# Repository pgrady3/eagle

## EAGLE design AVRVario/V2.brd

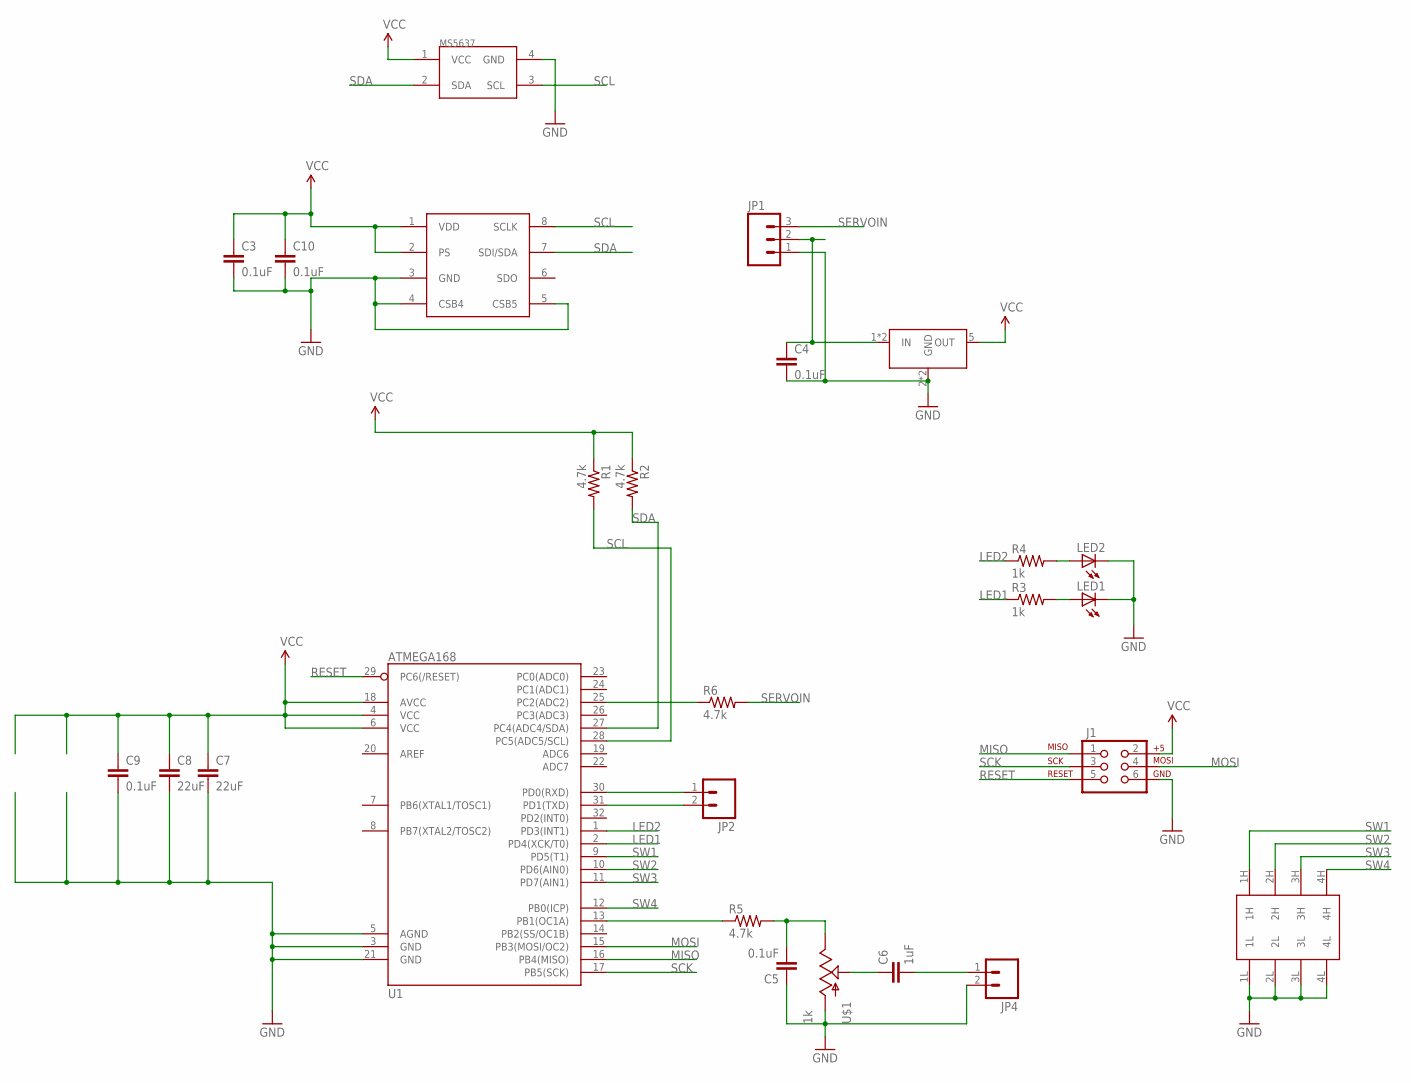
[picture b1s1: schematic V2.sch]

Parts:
C3, C4, C5, C9, C10: 0.1uF; 0603-CAP
C6: 1uF; 0603-CAP
C7, C8: 22uF; 0805
J1: AVR_SPI_PRG_6NS; 2X3-NS
JP1: M03PTH; 1X03
JP2, JP4: M02PTH; 1X02
LED1, LED2: LED0603; LED-0603
R1, R2, R5, R6: 4.7k; 0603-RES
R3, R4: 1k; 0603-RES
U1: ATMEGA168; TQFP32-08
U$1: 1k; BOURNS_3306KPW
U$2: MS5611
U$3: LINEAR_REGSOT23-5_TOREX; SOT23-5
U$4: MS5637
U$5: DIP_SWITCH; DIPSWITCH4

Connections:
GND: C3.2, C4.2, C5.1, C7.2, C8.2, C9.2, C10.2, J1.6, JP1.1, JP4.2, LED1.C, LED2.C, U1.3 (GND), U1.5 (AGND), U1.21 (GND), U$1.3 (A), U$2.3 (GND), U$2.4 (CSB4), U$2.5 (CSB5), U$3.2 (GND), U$3.3 (GND), U$4.4 (GND), U$5.1L, U$5.2L, U$5.3L, U$5.4L
LED1: R3.1, U1.2 (PD4(XCK/T0))
LED2: R4.1, U1.1 (PD3(INT1))
MISO: J1.1, U1.16 (PB4(MISO))
MOSI: J1.4, U1.15 (PB3(MOSI/OC2))
unnamed: R6.1, U1.25 (PC2(ADC2))
unnamed: C4.1, JP1.2, U$3.1 (IN), U$3.4 (IN)
unnamed: JP2.1, U1.30 (PD0(RXD))
unnamed: LED2.A, R4.2
unnamed: LED1.A, R3.2
unnamed: JP2.2, U1.31 (PD1(TXD))
unnamed: R5.1, U1.13 (PB1(OC1A))
unnamed: C5.2, R5.2, U$1.1 (E)
unnamed: C6.1, U$1.2 (S)
unnamed: C6.2, JP4.1
RESET: J1.5, U1.29 (PC6(/RESET))
SCK: J1.3, U1.17 (PB5(SCK))
SCL: R1.2, U1.28 (PC5(ADC5/SCL)), U$2.8 (SCLK), U$4.3 (SCL)
SDA: R2.2, U1.27 (PC4(ADC4/SDA)), U$2.7 (SDI/SDA), U$4.2 (SDA)
SERVOIN: JP1.3, R6.2
SW1: U1.9 (PD5(T1)), U$5.1H
SW2: U1.10 (PD6(AIN0)), U$5.2H
SW3: U1.11 (PD7(AIN1)), U$5.3H
SW4: U1.12 (PB0(ICP)), U$5.4H
VCC: C3.1, C7.1, C8.1, C9.1, C10.1, J1.2, R1.1, R2.1, U1.4 (VCC), U1.6 (VCC), U1.18 (AVCC), U$2.1 (VDD), U$2.2 (PS), U$3.5 (OUT), U$4.1 (VCC)

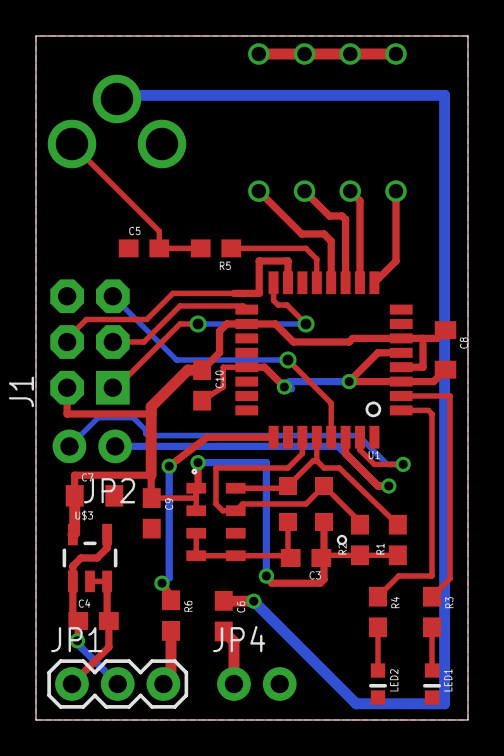
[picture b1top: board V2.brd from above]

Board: 2 copper layers, 24.0 x 38.0 mm, 26 parts (0 on the bottom side), 25 nets.

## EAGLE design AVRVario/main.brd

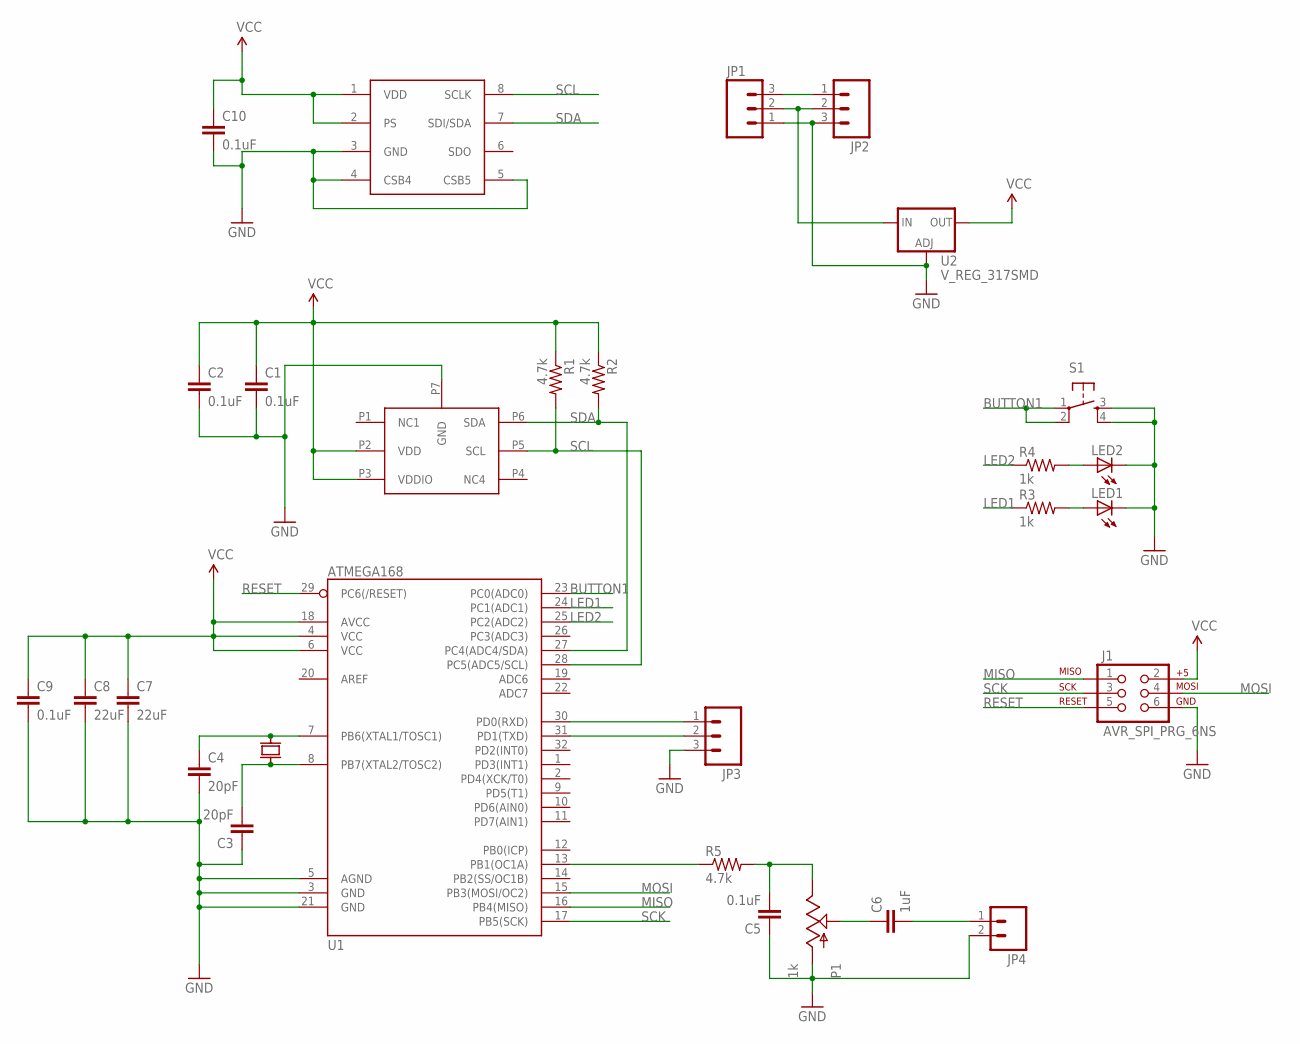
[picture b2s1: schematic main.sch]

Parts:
C1, C2, C5, C9, C10: 0.1uF; 0603-CAP
C3, C4: 20pF; 0603-CAP
C6: 1uF; 0603-CAP
C7, C8: 22uF; 0805
J1: AVR_SPI_PRG_6NS; 2X3-NS
JP1, JP2, JP3: M03PTH; 1X03
JP4: M02PTH; 1X02
LED1, LED2: LED0603; LED-0603
P1: 1k; TRIM_POT
R1, R2, R5: 4.7k; 0603-RES
R3, R4: 1k; 0603-RES
S1: TAC_SWITCHSMD; TACTILE_SWITCH_SMD
U1: ATMEGA168; TQFP32-08
U2: V_REG_317SMD; SOT223
U$1: BMP180
U$2: MS5611
U$3: 16M; HC49/US_7X4

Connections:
BUTTON1: S1.1, S1.2, U1.23 (PC0(ADC0))
GND: C1.2, C2.2, C3.1, C4.2, C5.1, C7.2, C8.2, C9.2, C10.2, J1.6, JP1.1, JP2.3, JP3.3, JP4.2, LED1.C, LED2.C, P1.3 (A), S1.3, S1.4, U1.3 (GND), U1.5 (AGND), U1.21 (GND), U2.1 (ADJ), U$1.P7 (GND), U$2.3 (GND), U$2.4 (CSB4), U$2.5 (CSB5)
LED1: R3.1, U1.24 (PC1(ADC1))
LED2: R4.1, U1.25 (PC2(ADC2))
MISO: J1.1, U1.16 (PB4(MISO))
MOSI: J1.4, U1.15 (PB3(MOSI/OC2))
unnamed: JP1.3, JP2.1
unnamed: C4.1, U1.7 (PB6(XTAL1/TOSC1)), U$3.P2
unnamed: C3.2, U1.8 (PB7(XTAL2/TOSC2)), U$3.P1
unnamed: JP1.2, JP2.2, U2.3 (IN)
unnamed: JP3.1, U1.30 (PD0(RXD))
unnamed: LED2.A, R4.2
unnamed: LED1.A, R3.2
unnamed: JP3.2, U1.31 (PD1(TXD))
unnamed: R5.1, U1.13 (PB1(OC1A))
unnamed: C5.2, P1.2 (E), R5.2
unnamed: C6.1, P1.1 (S)
unnamed: C6.2, JP4.1
RESET: J1.5, U1.29 (PC6(/RESET))
SCK: J1.3, U1.17 (PB5(SCK))
SCL: R1.2, U1.28 (PC5(ADC5/SCL)), U$1.P5 (SCL), U$2.8 (SCLK)
SDA: R2.2, U1.27 (PC4(ADC4/SDA)), U$1.P6 (SDA), U$2.7 (SDI/SDA)
VCC: C1.1, C2.1, C7.1, C8.1, C9.1, C10.1, J1.2, R1.1, R2.1, U1.4 (VCC), U1.6 (VCC), U1.18 (AVCC), U2.2 (OUT), U$1.P2 (VDD), U$1.P3 (VDDIO), U$2.1 (VDD), U$2.2 (PS)

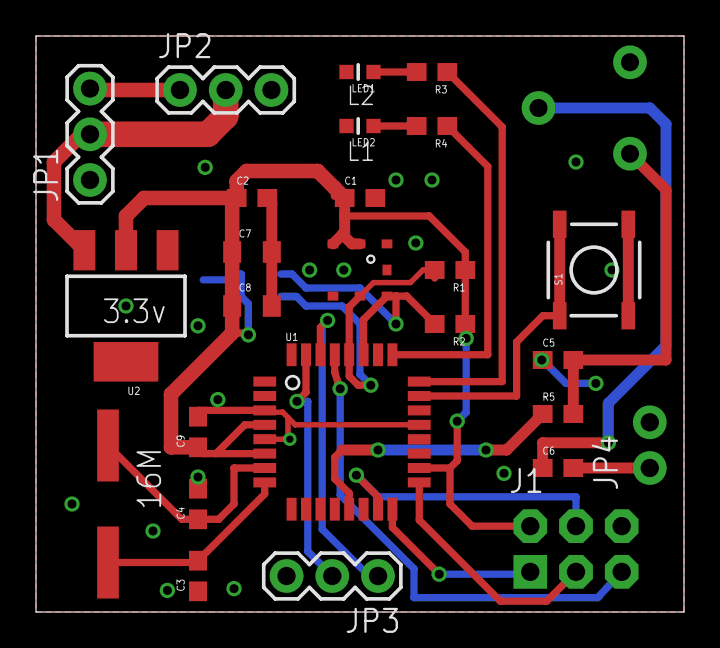
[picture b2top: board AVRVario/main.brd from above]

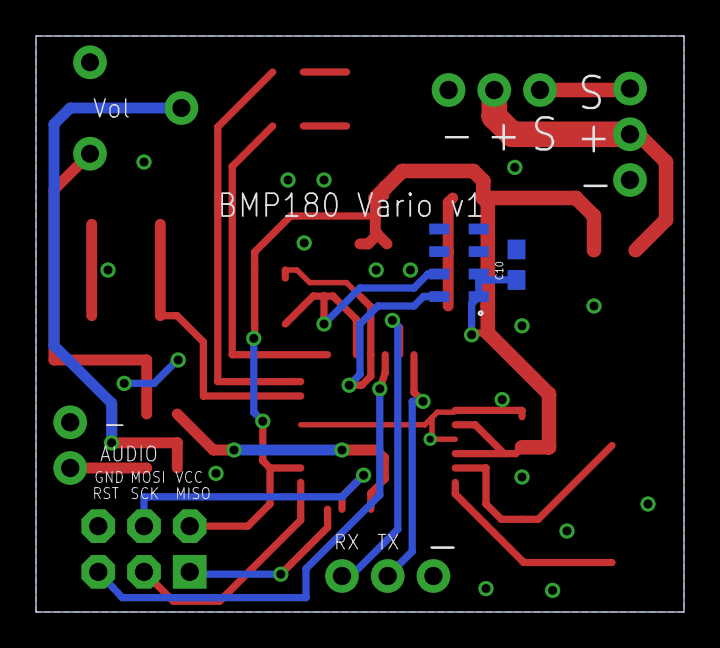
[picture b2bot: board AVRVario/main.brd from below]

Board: 2 copper layers, 36.0 x 32.0 mm, 29 parts (2 on the bottom side), 23 nets.

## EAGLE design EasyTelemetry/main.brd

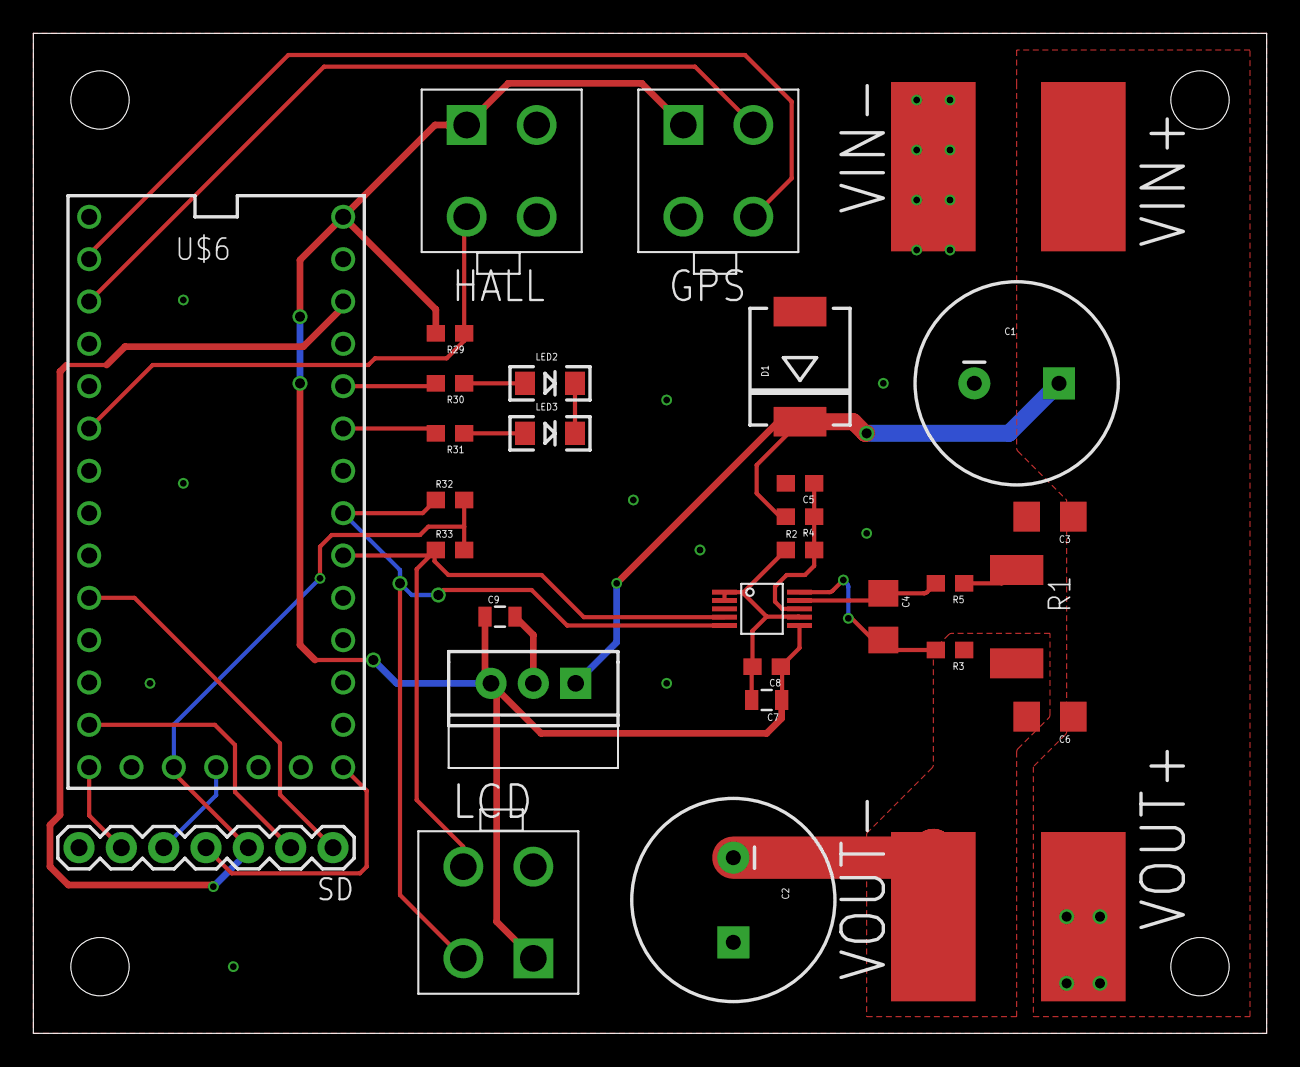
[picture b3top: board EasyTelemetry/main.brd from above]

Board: 2 copper layers, 74.0 x 60.0 mm, 37 parts (0 on the bottom side), 21 nets.

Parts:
C1, C2: 220uF; CPOL-RADIAL-1000UF-25V
C3, C4, C6: 1uF; 1206
C5, C8: 0.1uF; 0603-CAP
C7, C9: 10uF; 0805
D1: 3A/600V; SMC
GPS: GPS; 4PINVALULOK
HALL: HEADER4VALULOK; 4PINVALULOK
IC1: TO220-IGO
LCD: GPS; 4PINVALULOK
LED2, LED3: LED-1206
R1: 0.001; R2512
R2, R4: 47k; 0603-RES
R3, R5: 10; 0603-RES
R29, R32, R33: 2.2k; 0603-RES
R30, R31: 100; 0603-RES
SD: 1X07
U$1: INA226; PSOP-10
U$2, U$3, U$4, U$5: PAD
U$6: TEENSY_3.0_BASIC
U$13, U$14, U$15, U$16: SCREW; M3HOLE

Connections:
3.3: R32.2, R33.2, SD.3, U$6.3.3V, U$6.3.3V1
GND: C1.-, C3.2, C5.2, C7.2, C8.2, C9.2, D1.A, GPS.2, HALL.3, IC1.GND, LCD.2, LED2.C, LED3.C, R1.1, R2.1, R5.1, SD.5, U$1.1, U$1.2, U$1.7, U$3.PAD, U$6.AGND, U$6.GND, U$6.GND1
HALL: HALL.2, R29.1, U$6.4
LED1: R30.2, U$6.22/A8
LED2: R31.2, U$6.21/A7
MISO: SD.6, U$6.12
MOSI: SD.2, U$6.11
unnamed: C5.1, R2.2, R4.1, U$1.8
unnamed: LED2.A, R30.1
unnamed: LED3.A, R31.1
RX1: GPS.4, U$6.0
SCK: SD.4, U$6.13
SCL: LCD.3, R32.1, U$1.5, U$6.19/A5
SDA: LCD.4, R33.1, U$1.4, U$6.18/A4
SD_CS: SD.1, U$6.8
TX1: GPS.3, U$6.1
VCC: C7.1, C8.1, C9.1, GPS.1, HALL.1, IC1.OUT, LCD.1, R29.2, U$1.6, U$6.VIN
V_BAT: C1.+, C2.+, C3.1, C6.1, D1.C, IC1.IN, R4.2, U$2.PAD, U$4.PAD
V_GND_OUT: C2.-, C6.2, R1.2, R3.1, U$5.PAD
V_SENSE+: C4.2, R3.2, U$1.10
V_SENSE-: C4.1, R5.2, U$1.9

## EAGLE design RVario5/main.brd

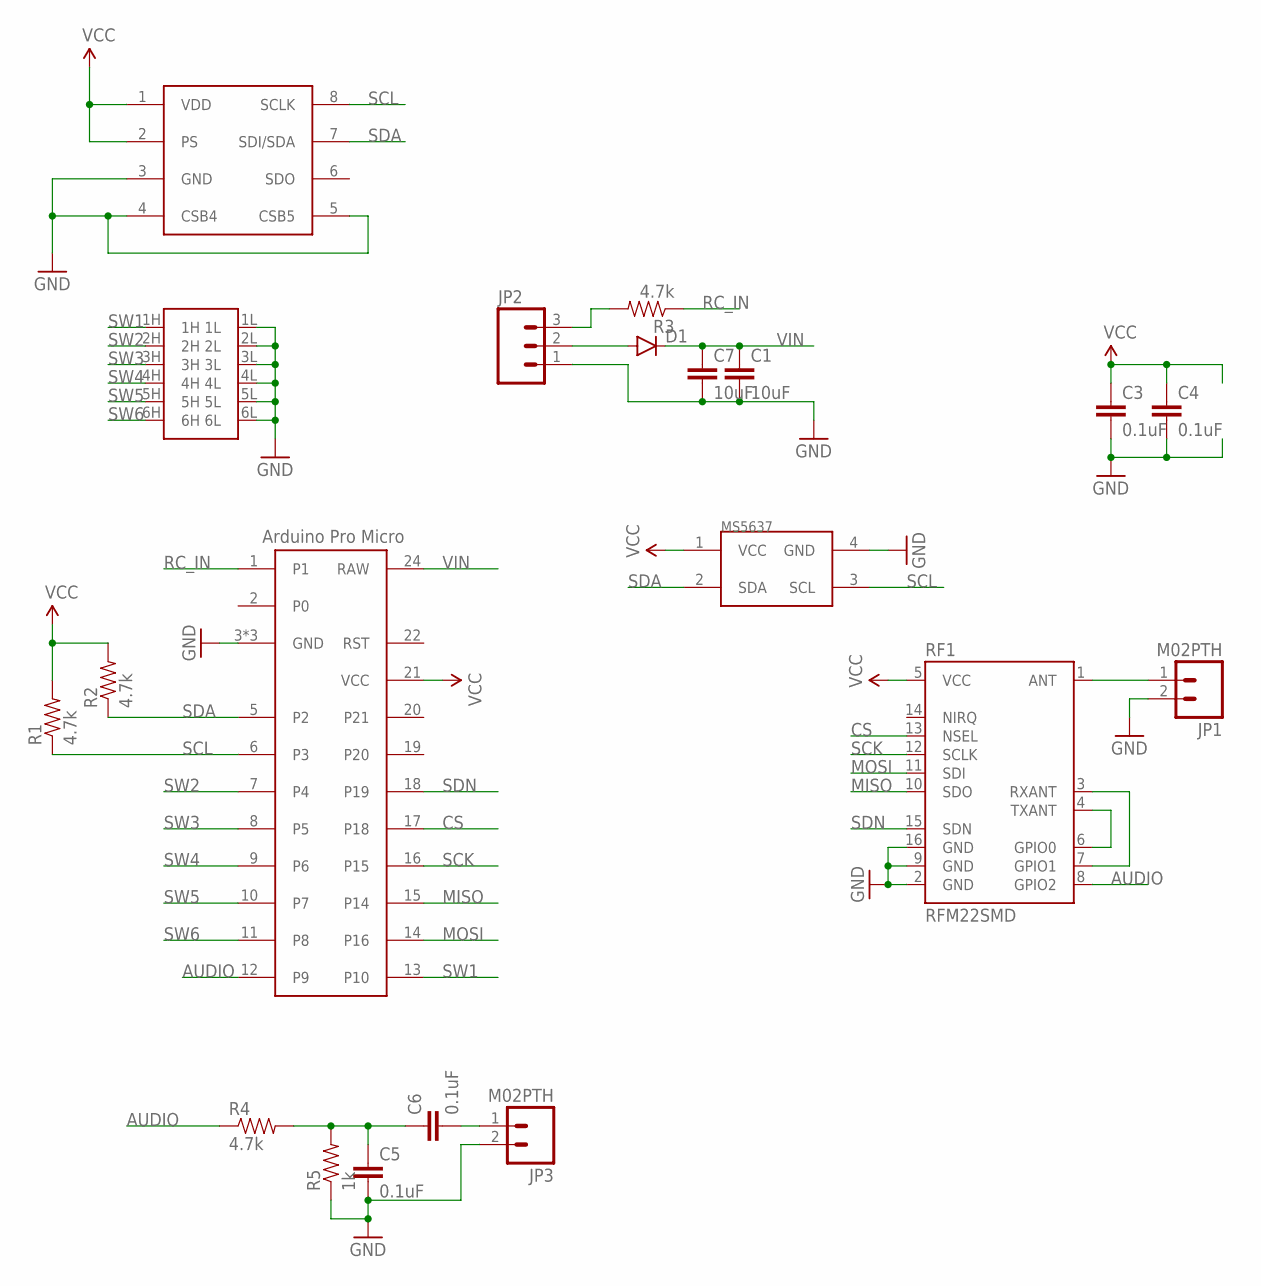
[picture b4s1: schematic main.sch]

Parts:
C1, C7: 10uF; 0805
C3, C4, C5, C6: 0.1uF; 0603-CAP
D1: DIODESMA; SMA-DIODE
JP1, JP3: M02PTH; 1X02
JP2: M03PTH; 1X03
R1, R2, R3, R4: 4.7k; 0603-RES
R5: 1k; 0603-RES
RF1: RFM22SMD; RFM22-XXX-S2
U$1: PRO_MICRO
U$2: DIPSWITCH6
U$3: MS5637
U$4: MS5611

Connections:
AUDIO: R4.1, RF1.8 (GPIO2), U$1.12 (P9)
CS: RF1.13 (NSEL), U$1.17 (P18)
GND: C1.2, C3.2, C4.2, C5.2, C7.2, JP1.2, JP2.1, JP3.2, R5.1, RF1.2 (GND), RF1.9 (GND), RF1.16 (GND), U$1.3 (GND), U$1.4 (GND), U$1.23 (GND), U$2.1L, U$2.2L, U$2.3L, U$2.4L, U$2.5L, U$2.6L, U$3.4 (GND), U$4.3 (GND), U$4.4 (CSB4), U$4.5 (CSB5)
MISO: RF1.10 (SDO), U$1.15 (P14)
MOSI: RF1.11 (SDI), U$1.14 (P16)
unnamed: JP1.1, RF1.1 (ANT)
unnamed: JP2.3, R3.2
unnamed: D1.A, JP2.2
unnamed: RF1.4 (TXANT), RF1.6 (GPIO0)
unnamed: RF1.3 (RXANT), RF1.7 (GPIO1)
unnamed: C5.1, C6.1, R4.2, R5.2
unnamed: C6.2, JP3.1
RC_IN: R3.1, U$1.1
SCK: RF1.12 (SCLK), U$1.16 (P15)
SCL: R1.1, U$1.6 (P3), U$3.3 (SCL), U$4.8 (SCLK)
SDA: R2.1, U$1.5 (P2), U$3.2 (SDA), U$4.7 (SDI/SDA)
SDN: RF1.15 (SDN), U$1.18 (P19)
SW1: U$1.13 (P10), U$2.1H
SW2: U$1.7 (P4), U$2.2H
SW3: U$1.8 (P5), U$2.3H
SW4: U$1.9 (P6), U$2.4H
SW5: U$1.10 (P7), U$2.5H
SW6: U$1.11 (P8), U$2.6H
VCC: C3.1, C4.1, R1.2, R2.2, RF1.5 (VCC), U$1.21 (VCC), U$3.1 (VCC), U$4.1 (VDD), U$4.2 (PS)
VIN: C1.1, C7.1, D1.C, U$1.24 (RAW)

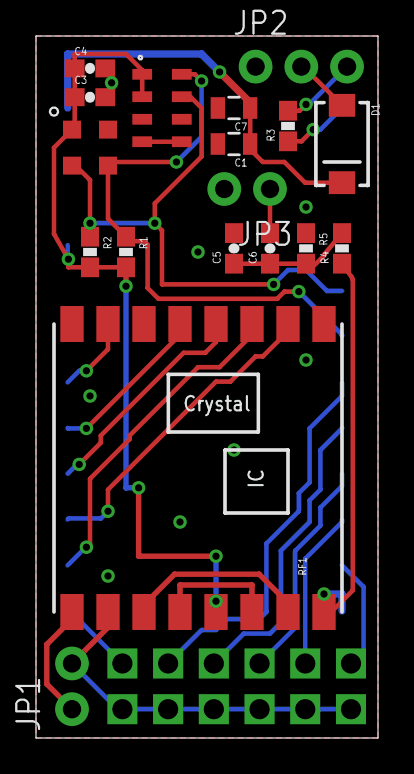
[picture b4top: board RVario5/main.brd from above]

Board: 2 copper layers, 19.0 x 39.0 mm, 20 parts (1 on the bottom side), 25 nets.

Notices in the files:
parts and their libraries:
SparkFun-DigitalIC: Licensing: CC v3.0 Share-Alike You are welcome to use this library for commercial purposes.
SparkFun-Capacitors: Licensing: Creative Commons ShareAlike 4.0 International - https://creativecommons.org/licenses/by-sa/4.0
